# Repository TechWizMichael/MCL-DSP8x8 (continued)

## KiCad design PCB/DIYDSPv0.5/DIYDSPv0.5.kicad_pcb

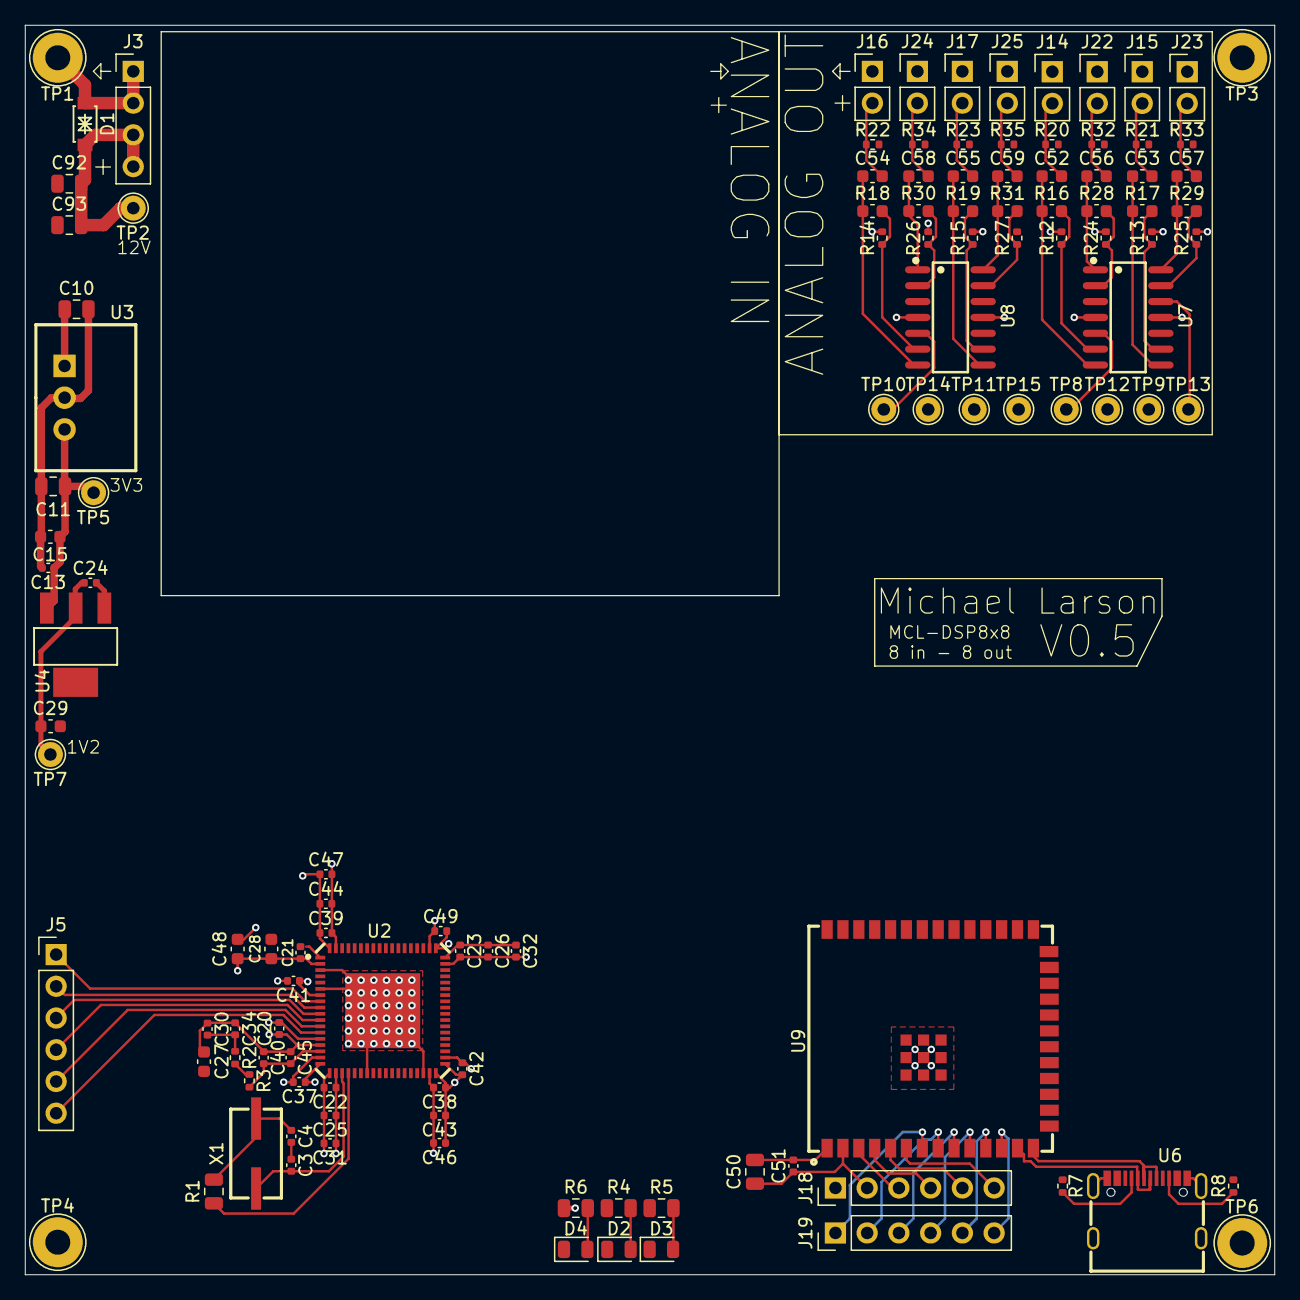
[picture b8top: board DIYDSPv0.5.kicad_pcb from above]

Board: 4 copper layers, 100.0 x 100.0 mm, 116 parts (0 on the bottom side), 69 nets.

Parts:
C3, C4: 22p; C_0402_1005Metric
C10, C11, C50, C92, C93: 22u; C_0805_2012Metric
C13, C20, C21, C24, C25, C26, C37, C41, C42, C43, C44, C49, C51: 100n; C_0402_1005Metric
C15, C27, C28, C29, C48, C52, C53, C54, C55, C56, C57, C58, C59: 10u; C_0603_1608Metric
C22, C23, C38, C39: 10n; C_0402_1005Metric
C30: 4.7n; C_0402_1005Metric
C31, C32, C46, C47: 1u; C_0402_1005Metric
C34: 1n; C_0402_1005Metric
C40: 100p; C_0402_1005Metric
C45: 47p; C_0402_1005Metric
D1: SMF20CA
D2, D3, D4: LED; LED_0805_2012Metric
J3: Conn_01x04; PinHeader_1x04_P2.54mm_Vertical
J5, J18, J19: Conn_01x06; PinHeader_1x06_P2.54mm_Vertical
J14, J15, J16, J17, J22, J23, J24, J25: Conn_01x02; PinHeader_1x02_P2.54mm_Vertical
R1, R4, R5, R6: 100; C_0805_2012Metric
R2, R3: 2.2k; R_0402_1005Metric
R7, R8: 5.1k; R_0402_1005Metric
R12, R13, R14, R15, R20, R21, R22, R23, R24, R25, R26, R27, R32, R33, R34, R35: 100k; R_0402_1005Metric
R16, R17, R18, R19, R28, R29, R30, R31: 220k; C_0603_1608Metric
TP1, TP3, TP4, TP6: TestPoint; TestPoint_THTPad_D4.0mm_Drill2.0mm
TP2, TP5, TP7, TP8, TP9, TP10, TP11, TP12, TP13, TP14, TP15: TestPoint; TestPoint_THTPad_D2.0mm_Drill1.0mm
U2: ADAU1452; ADAU1452WBCPZ-RL
U3: K7803M-1000R3
U4: AMS1117-1.2
U6: GT-USB-7010ASV
U7, U8: LM324DT
U9: ESP32-S3-WROOM-1U-N8
X1: 12.288MHz; S47SMD12.288M20PF20R30B3

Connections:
+1V2: C22.1, C23.2, C24.1, C25.1, C26.2, C29.1, C31.1, C32.2, C38.2, C39.2, C43.2, C44.2, C46.2, C47.2, TP7.1, U2.20 (DVDD), U2.35 (DVDD), U2.53 (DVDD), U2.71 (DVDD), U4.2 (OUT)
+3V3: C11.1, C13.1, C15.1, C20.1, C21.1, C27.1, C28.1, C30.1, C34.1, C37.1, C40.1, C41.1, C42.1, C45.1, C48.1, C49.1, C50.1, C51.1, J18.2, R6.1, TP5.1, U2.2 (IOVDD), U2.7 (AVDD), U2.15 (PVDD), U2.18 (IOVDD), U2.38 (IOVDD), U2.56 (IOVDD), U3.3 (Vo), U4.3 (IN), U9.2 (3V3)
+12V: C10.1, C92.2, C93.2, D1.2, J3.3, J3.4, TP2.1, U3.1 (Vin), U7.4 (VCC+), U8.4 (VCC+)
/AOUT1: TP10.1, U8.5 (IN2+)
/AOUT2: TP14.1, U8.3 (IN1+)
/AOUT3: TP11.1, U8.10 (IN3+)
/AOUT4: TP15.1, U8.12 (IN4+)
/AOUT5: TP8.1, U7.5 (IN2+)
/AOUT6: TP12.1, U7.3 (IN1+)
/AOUT7: TP9.1, U7.10 (IN3+)
/AOUT8: TP13.1, U7.12 (IN4+)
/AUXADC0: J5.1, U2.8 (AUXADC0)
/AUXADC1: J5.2, U2.9 (AUXADC1)
/AUXADC2: J5.3, U2.10 (AUXADC2)
/AUXADC3: J5.4, U2.11 (AUXADC3)
/AUXADC4: J5.5, U2.12 (AUXADC4)
/AUXADC5: J5.6, U2.13 (AUXADC5)
/BCLK_OUT0: U2.40 (BCLK_OUT0), U2.57 (BCLK_IN0)
/BCLK_OUT1: U2.43 (BCLK_OUT1), U2.60 (BCLK_IN1)
/IO4: J18.4, U9.4 (IO4)
/IO5: J18.5, U9.5 (IO5)
/IO6: J18.6, U9.6 (IO6)
/IO7: J19.1, U9.7 (IO7)
/IO8: J19.6, U9.12 (IO8)
/IO15: J19.2, U9.8 (IO15)
/IO16: J19.3, U9.9 (IO16)
/IO17: J19.4, U9.10 (IO17)
/IO18: J19.5, U9.11 (IO18)
/LRCLK_OUT0: U2.39 (LRCLK_OUT0/MP4), U2.58 (LRCLK_IN0/MP10)
/LRCLK_OUT1: U2.42 (LRCLK_OUT1/MP5), U2.61 (LRCLK_IN1/MP11)
/PLLFILT: C40.2, C45.2, R3.2, U2.16 (PLLFILT)
/USB_DN: U6.A7 (DN1), U6.B7 (DN2), U9.13 (IO19)
/USB_DP: U6.A6 (DP1), U6.B6 (DP2), U9.14 (IO20)
/XTALIN: C3.2, U2.21 (XTALIN/MCLK), X1.2
/XTALOUT: R1.1, U2.22 (XTALOUT)
/uC_EN: J18.3, U9.3 (EN)
GND: C3.1, C4.2, C10.2, C11.2, C13.2, C15.2, C20.2, C21.2, C22.2, C23.1, C24.2, C25.2, C26.1, C27.2, C28.2, C29.2, C31.2, C32.1, C37.2, C38.1, C39.1, C41.2, C42.2, C43.1, C44.1, C46.1, C47.1, C48.2, C49.2, C50.2, C51.2, C92.1, C93.1, D1.1, D2.1 (K), D3.1 (K), D4.1 (K), J3.1, J3.2, J14.1, J15.1, J16.1, J17.1, J18.1, J22.1, J23.1, J24.1, J25.1, R7.2, R8.2, R12.2, R13.2, R14.2, R15.2, R20.2, R21.2, R22.2, R23.2, R24.2, R25.2, R26.2, R27.2, R32.2, R33.2, R34.2, R35.2, TP1.1, TP3.1, TP4.1, TP6.1, U2.1 (DGND), U2.3 (VDRIVE), U2.6 (AGND), U2.14 (PGND), U2.17 (DGND), U2.19 (DGND), U2.25 (DGND), U2.34 (SELFBOOT), U2.36 (DGND), U2.37 (DGND), U2.54 (DGND), U2.55 (DGND), U2.72 (DGND), U2.73 (EP), U3.2 (GND), U4.1 (ADJ/GND), U6.1 (SHELL), U6.2 (SHELL), U6.3 (SHELL), U6.4 (SHELL), U6.A1B12 (GND), U6.B1A12 (GND), U7.11 (VCC-), U8.11 (VCC-), U9.1 (GND), U9.40 (GND), U9.41 (GND)
unnamed: C4.1, R1.2, X1.1
unnamed: C30.2, C34.2, R2.1
unnamed: D2.2 (A), R4.2
unnamed: D3.2 (A), R5.2
unnamed: D4.2 (A), R6.2
unnamed: C52.2, J14.2, R20.1
unnamed: C53.2, J15.2, R21.1
unnamed: C54.2, J16.2, R22.1
unnamed: C55.2, J17.2, R23.1
unnamed: C56.2, J22.2, R32.1
unnamed: C57.2, J23.2, R33.1
unnamed: C58.2, J24.2, R34.1
unnamed: C59.2, J25.2, R35.1
unnamed: R2.2, R3.1
unnamed: R7.1, U6.A5 (CC1)
unnamed: R8.1, U6.B5 (CC2)
unnamed: R24.1, R28.2, U7.2 (IN1-)
unnamed: C56.1, R28.1, U7.1 (OUT1)
unnamed: R12.1, R16.2, U7.6 (IN2-)
unnamed: C52.1, R16.1, U7.7 (OUT2)
unnamed: R13.1, R17.2, U7.9 (IN3-)
unnamed: C53.1, R17.1, U7.8 (OUT3)
unnamed: R25.1, R29.2, U7.13 (IN4-)
unnamed: C57.1, R29.1, U7.14 (OUT4)
unnamed: R26.1, R30.2, U8.2 (IN1-)
unnamed: C58.1, R30.1, U8.1 (OUT1)
unnamed: R14.1, R18.2, U8.6 (IN2-)
unnamed: C54.1, R18.1, U8.7 (OUT2)
unnamed: R15.1, R19.2, U8.9 (IN3-)
unnamed: C55.1, R19.1, U8.8 (OUT3)
unnamed: R27.1, R31.2, U8.13 (IN4-)
unnamed: C59.1, R31.1, U8.14 (OUT4)

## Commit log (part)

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2026-03-14 v0.4 PCB - Partial Breakout
    This is the KiCad project for the first board that I ordered for testing
2026-03-14 Delete DIYDSPv0.4 directory
    Figuring out Git
2026-03-14 Added all PCB revisions
2026-03-14 Started Arduino code/firmware
2026-03-21 Added Initial Firmware
2026-03-21 Update LICENSE
2026-03-25 Successful Programming of ESP32 and ADAU1452. Testing in progress for AK4619VN
2026-03-25 Specified I2C Speed
2026-04-01 Changes from testing first prototype (ADAU1452 Firmware is currently the Test firmware)
2026-04-29 PCB V0.6 for second prototype
2026-04-29 Sent off for production
2026-05-12 New prototype design
2026-05-13 Cleaned folders, cleaned firmware, v0.8 started.
2026-05-31 Successful programming of v0.7 board
